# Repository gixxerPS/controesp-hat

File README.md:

# controesp
controllino like board for esp

## PCB size

- base
86.5 x 84 mm
- hat
57 x 80 mm

## parts

- relais output connector plug
C504919 (Ningbo 5,08mm 15A/300V 2,5qmm)

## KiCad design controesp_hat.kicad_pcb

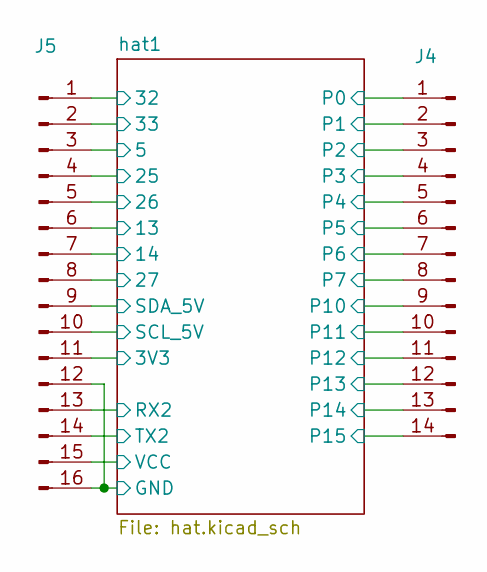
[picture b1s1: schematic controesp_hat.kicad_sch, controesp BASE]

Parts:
J4: Conn_01x14_Pin; PinHeader_1x14_P2.54mm_Vertical
J5: Conn_01x16_Pin; PinHeader_1x16_P2.54mm_Vertical

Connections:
/controesp_hat/3V3: J5.11; also elsewhere on the board
/controesp_hat/5: J5.3; also elsewhere on the board
/controesp_hat/13: J5.6; also elsewhere on the board
/controesp_hat/14: J5.7; also elsewhere on the board
/controesp_hat/25: J5.4; also elsewhere on the board
/controesp_hat/26: J5.5; also elsewhere on the board
/controesp_hat/27: J5.8; also elsewhere on the board
/controesp_hat/32: J5.1; also elsewhere on the board
/controesp_hat/33: J5.2; also elsewhere on the board
/controesp_hat/GND: J5.12, J5.16; also elsewhere on the board
/controesp_hat/P0: J4.1; also elsewhere on the board
/controesp_hat/P1: J4.2; also elsewhere on the board
/controesp_hat/P2: J4.3; also elsewhere on the board
/controesp_hat/P3: J4.4; also elsewhere on the board
/controesp_hat/P4: J4.5; also elsewhere on the board
/controesp_hat/P5: J4.6; also elsewhere on the board
/controesp_hat/P6: J4.7; also elsewhere on the board
/controesp_hat/P7: J4.8; also elsewhere on the board
/controesp_hat/P10: J4.9; also elsewhere on the board
/controesp_hat/P11: J4.10; also elsewhere on the board
/controesp_hat/P12: J4.11; also elsewhere on the board
/controesp_hat/P13: J4.12; also elsewhere on the board
/controesp_hat/P14: J4.13; also elsewhere on the board
/controesp_hat/P15: J4.14; also elsewhere on the board
/controesp_hat/RX2: J5.13; also elsewhere on the board
/controesp_hat/SCL_5V: J5.10; also elsewhere on the board
/controesp_hat/SDA_5V: J5.9; also elsewhere on the board
/controesp_hat/TX2: J5.14; also elsewhere on the board
/controesp_hat/VCC: J5.15; also elsewhere on the board

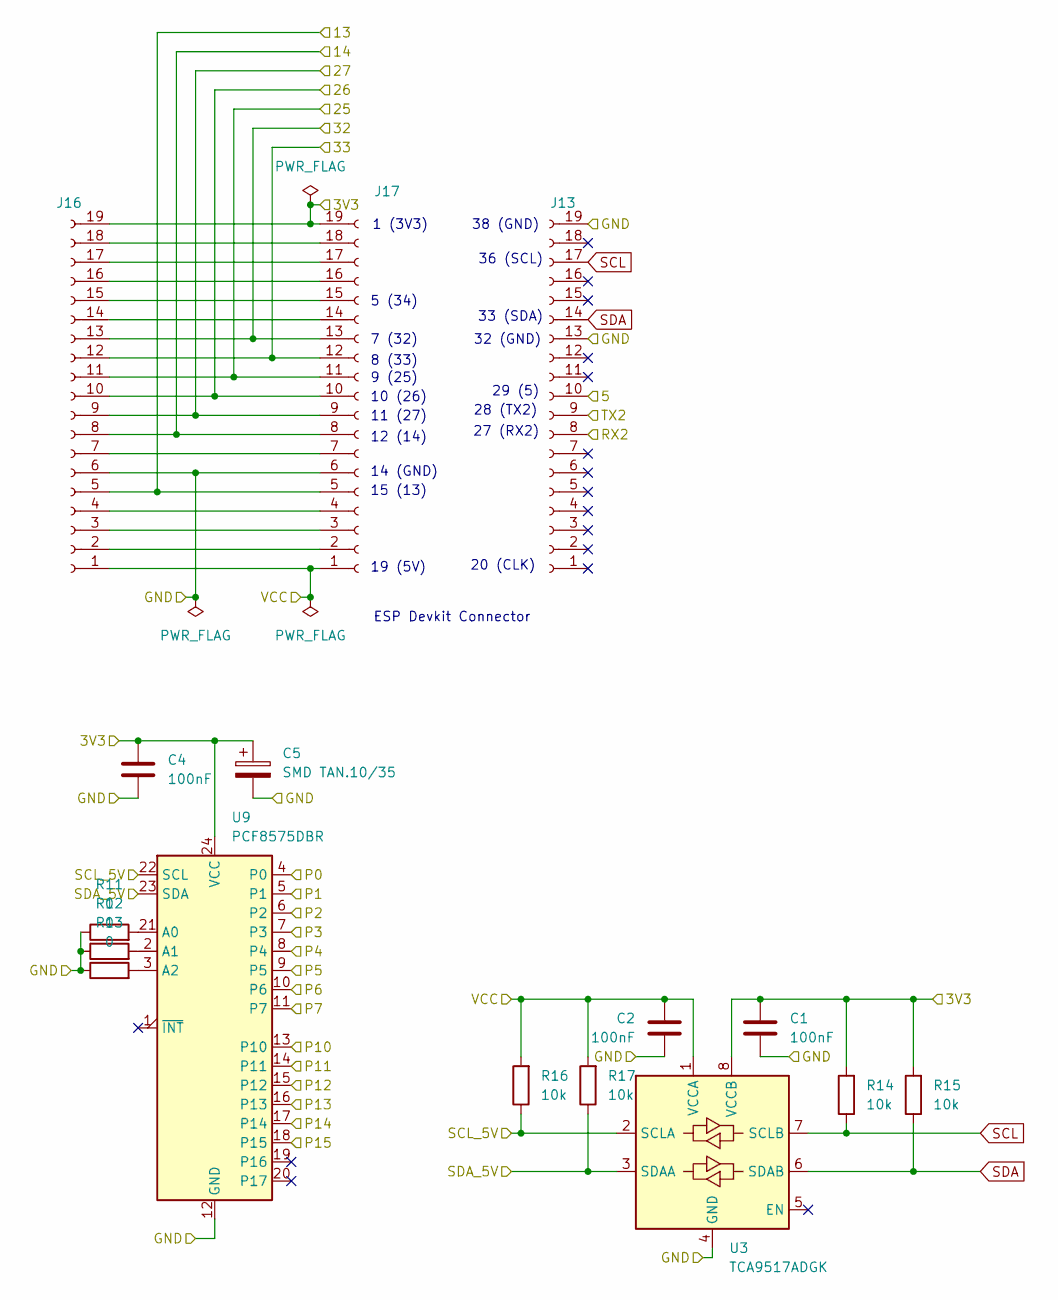
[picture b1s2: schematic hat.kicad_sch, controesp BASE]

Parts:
C1, C2, C4: 100nF; C_0805_2012Metric_Pad1.18x1.45mm_HandSolder; LCSC C49678
C5: SMD TAN.10/35; C_0805_2012Metric_Pad1.18x1.45mm_HandSolder; LCSC C15850
J13, J16, J17: Conn_01x19_Socket; PinSocket_1x19_P2.54mm_Vertical; LCSC C319202
R11, R12, R13: 0; R_0805_2012Metric_Pad1.20x1.40mm_HandSolder; LCSC C17477
R14, R15, R16, R17: 10k; R_0805_2012Metric_Pad1.20x1.40mm_HandSolder; LCSC C17414
U3: TCA9517ADGK; VSSOP-8_3x3mm_P0.65mm; LCSC C544515
U9: PCF8575DBR; SSOP-24_5.3x8.2mm_P0.65mm; LCSC C2863388

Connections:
/controesp_hat/3V3: C1.1, C4.1, C5.1, J16.19, J17.19, R14.2, R15.2, U3.8 (VCCB), U9.24 (VCC); also elsewhere on the board
/controesp_hat/5: J13.10; also elsewhere on the board
/controesp_hat/13: J16.5, J17.5; also elsewhere on the board
/controesp_hat/14: J16.8, J17.8; also elsewhere on the board
/controesp_hat/25: J16.11, J17.11; also elsewhere on the board
/controesp_hat/26: J16.10, J17.10; also elsewhere on the board
/controesp_hat/27: J16.9, J17.9; also elsewhere on the board
/controesp_hat/32: J16.13, J17.13; also elsewhere on the board
/controesp_hat/33: J16.12, J17.12; also elsewhere on the board
/controesp_hat/GND: C1.2, C2.2, C4.2, C5.2, J13.13, J13.19, J16.6, J17.6, R11.1, R12.1, R13.1, U3.4 (GND), U9.12 (GND); also elsewhere on the board
/controesp_hat/P0: U9.4 (P0); also elsewhere on the board
/controesp_hat/P1: U9.5 (P1); also elsewhere on the board
/controesp_hat/P2: U9.6 (P2); also elsewhere on the board
/controesp_hat/P3: U9.7 (P3); also elsewhere on the board
/controesp_hat/P4: U9.8 (P4); also elsewhere on the board
/controesp_hat/P5: U9.9 (P5); also elsewhere on the board
/controesp_hat/P6: U9.10 (P6); also elsewhere on the board
/controesp_hat/P7: U9.11 (P7); also elsewhere on the board
/controesp_hat/P10: U9.13 (P10); also elsewhere on the board
/controesp_hat/P11: U9.14 (P11); also elsewhere on the board
/controesp_hat/P12: U9.15 (P12); also elsewhere on the board
/controesp_hat/P13: U9.16 (P13); also elsewhere on the board
/controesp_hat/P14: U9.17 (P14); also elsewhere on the board
/controesp_hat/P15: U9.18 (P15); also elsewhere on the board
/controesp_hat/RX2: J13.8; also elsewhere on the board
/controesp_hat/SCL_5V: R16.1, U3.2 (SCLA), U9.22 (SCL); also elsewhere on the board
/controesp_hat/SDA_5V: R17.1, U3.3 (SDAA), U9.23 (SDA); also elsewhere on the board
/controesp_hat/TX2: J13.9; also elsewhere on the board
/controesp_hat/VCC: C2.1, J16.1, J17.1, R16.2, R17.2, U3.1 (VCCA); also elsewhere on the board
unnamed: J16.2, J17.2
unnamed: J16.3, J17.3
unnamed: J16.4, J17.4
unnamed: J16.7, J17.7
unnamed: J16.14, J17.14
unnamed: J16.15, J17.15
unnamed: J16.16, J17.16
unnamed: J16.17, J17.17
unnamed: J16.18, J17.18
unnamed: R11.2, U9.21 (A0)
unnamed: R12.2, U9.2 (A1)
unnamed: R13.2, U9.3 (A2)
SCL: J13.17, R14.1, U3.7 (SCLB)
SDA: J13.14, R15.1, U3.6 (SDAB)

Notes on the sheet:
19 (5V)
7 (32)
33 (SDA)
28 (TX2)
27 (RX2)
ESP Devkit Connector
8 (33)
29 (5)
5 (34)
14 (GND)
10 (26)
1 (3V3)
38 (GND)
11 (27)
12 (14)
9 (25)
15 (13)
36 (SCL)
32 (GND)
20 (CLK)

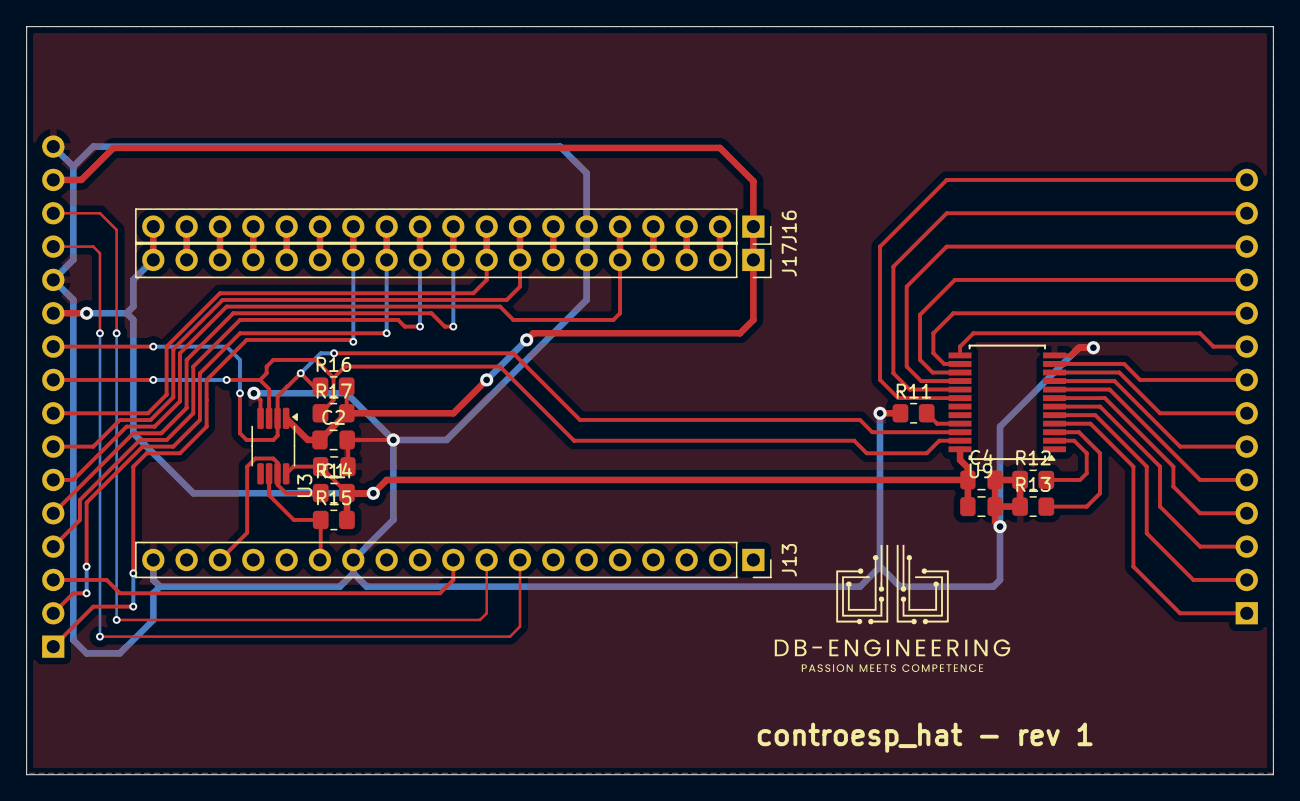
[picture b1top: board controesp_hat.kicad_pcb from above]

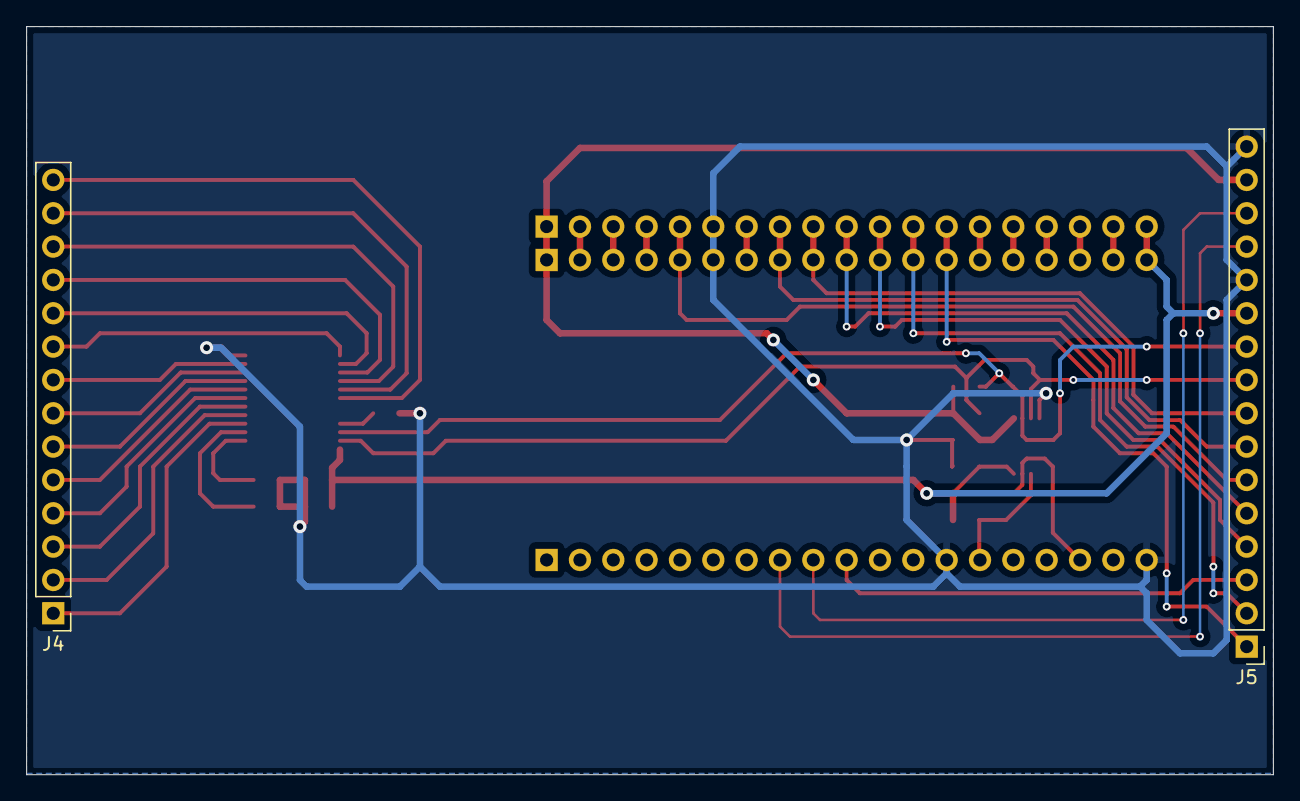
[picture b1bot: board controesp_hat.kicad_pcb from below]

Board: 2 copper layers, 95.0 x 57.0 mm, 18 parts (2 on the bottom side), 43 nets.

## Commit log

2025-04-21 splitted hat pcb into seperate proj
2025-04-23 rev01
2025-06-12 added artifacts
